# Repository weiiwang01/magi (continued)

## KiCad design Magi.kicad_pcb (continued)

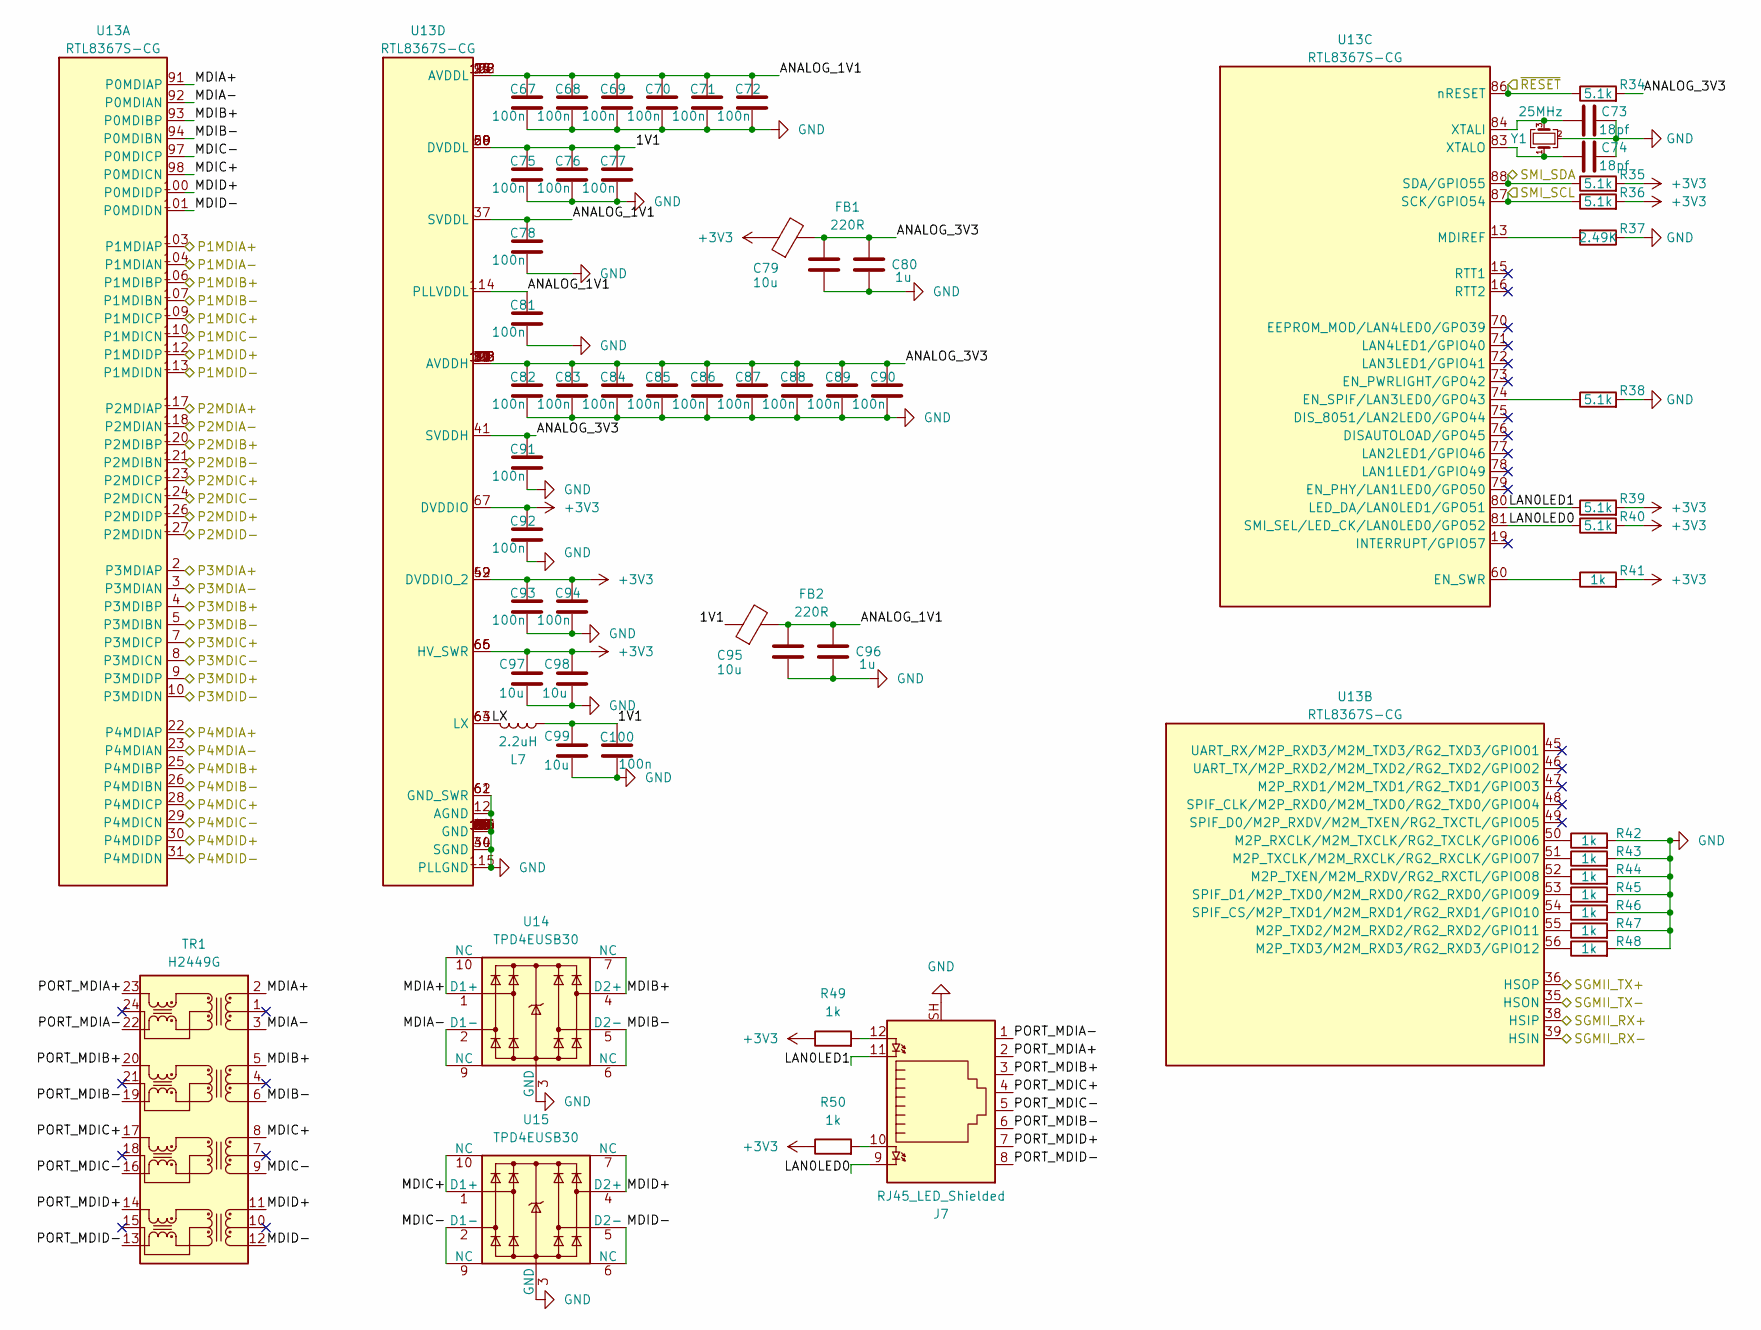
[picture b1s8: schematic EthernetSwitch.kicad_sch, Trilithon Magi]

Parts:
C67, C68, C69, C70, C71, C72, C75, C76, C77, C78, C81, C82, C83, C84, C85, C86, C87, C88, C89, C90, C91, C92, C93, C94, C100: 100n; C_0402_1005Metric; MPN CL05B104KB54PNC; LCSC C307331
C73, C74: 18pf; C_0402_1005Metric; MPN 0402CG180J500NT; LCSC C1549
C79, C95, C97, C98, C99: 10u; C_0603_1608Metric; MPN CL10A106MA8NRNC; LCSC C96446
C80, C96: 1u; C_0402_1005Metric; MPN CL05A105KO5NNNC; LCSC C29266
FB1, FB2: 220R; L_0603_1608Metric; MPN BLM18PG121SN1D; LCSC C14709
J7: RJ45_LED_Shielded; RJ45-TH_RJ45-005-202-11; MPN RJ45-005-202-11; LCSC C7421405
L7: 2.2uH; L_Changjiang_FTC404030S; MPN FTC404030S2R2MGCA; LCSC C39676081
R34, R35, R36, R38, R39, R40: 5.1k; R_0402_1005Metric; MPN 0402WGF5101TCE; LCSC C25905
R37: 2.49K; R_0402_1005Metric; MPN 0402WGF2491TCE; LCSC C25884
R41, R42, R43, R44, R45, R46, R47, R48, R49, R50: 1k; R_0402_1005Metric; MPN 0402WGF1001TCE; LCSC C11702
TR1: H2449G; RJ45-SMD_24P_L15.6-W8.7_H24308C; MPN H2449G; LCSC C5464748
U13: RTL8367S-CG; LQFP-128_14x14mm_P0.4mm; MPN RTL8367S-CG; LCSC C2760849
U14, U15: TPD4EUSB30; USON-10_2.5x1.0mm_P0.5mm; MPN TPD4EUSB30DQAR; LCSC C90627
Y1: 25MHz; Crystal_SMD_2016-4Pin_2.0x1.6mm; MPN XL7EL89COI-111YLC-25M; LCSC C20617996

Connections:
+3V3: C92.1, C93.1, C94.1, C97.1, C98.1, FB1.1, R35.2, R36.2, R39.2, R40.2, R41.2, R49.1, R50.1, U13.42 (DVDDIO_2), U13.59 (DVDDIO_2), U13.65 (HV_SWR), U13.66 (HV_SWR), U13.67 (DVDDIO); also elsewhere on the board
/Controller/ETH_P0+: U13.2 (P3MDIAP); also elsewhere on the board
/Controller/ETH_P0-: U13.3 (P3MDIAN); also elsewhere on the board
/Controller/ETH_P1+: U13.4 (P3MDIBP); also elsewhere on the board
/Controller/ETH_P1-: U13.5 (P3MDIBN); also elsewhere on the board
/Controller/PD7: R35.1, U13.88 (SDA/GPIO55); also elsewhere on the board
/Controller/PF10: R36.1, U13.87 (SCK/GPIO54); also elsewhere on the board
/Controller/PF11: R34.1, U13.86 (nRESET); also elsewhere on the board
/Ethernet Switch/1V1: C75.1, C76.1, C77.1, C99.1, C100.1, FB2.1, L7.2, U13.20 (DVDDL), U13.58 (DVDDL), U13.69 (DVDDL)
/Ethernet Switch/ANALOG_1V1: C67.1, C68.1, C69.1, C70.1, C71.1, C72.1, C78.1, C81.1, C95.1, C96.1, FB2.2, U13.6 (AVDDL), U13.14 (AVDDL), U13.27 (AVDDL), U13.37 (SVDDL), U13.95 (AVDDL), U13.108 (AVDDL), U13.114 (PLLVDDL), U13.122 (AVDDL)
/Ethernet Switch/ANALOG_3V3: C79.1, C80.1, C82.1, C83.1, C84.1, C85.1, C86.1, C87.1, C88.1, C89.1, C90.1, C91.1, FB1.2, R34.2, U13.11 (AVDDH), U13.17 (AVDDH), U13.21 (AVDDH), U13.33 (AVDDH), U13.41 (SVDDH), U13.82 (AVDDH), U13.90 (AVDDH), U13.102 (AVDDH), U13.116 (AVDDH), U13.128 (AVDDH)
/Ethernet Switch/LAN0LED0: J7.9, R40.1, U13.81 (SMI_SEL/LED_CK/LAN0LED0/GPO52)
/Ethernet Switch/LAN0LED1: J7.11, R39.1, U13.80 (LED_DA/LAN0LED1/GPO51)
/Ethernet Switch/LX: L7.1, U13.63 (LX), U13.64 (LX)
/Ethernet Switch/MDIA+: TR1.2 (TD1+), U13.91 (P0MDIAP), U14.1 (D1+), U14.10 (NC)
/Ethernet Switch/MDIA-: TR1.3 (TD1-), U13.92 (P0MDIAN), U14.2 (D1-), U14.9 (NC)
/Ethernet Switch/MDIB+: TR1.5 (TD2+), U13.93 (P0MDIBP), U14.4 (D2+), U14.7 (NC)
/Ethernet Switch/MDIB-: TR1.6 (TD2-), U13.94 (P0MDIBN), U14.5 (D2-), U14.6 (NC)
/Ethernet Switch/MDIC+: TR1.8 (TD3+), U13.98 (P0MDICN), U15.1 (D1+), U15.10 (NC)
/Ethernet Switch/MDIC-: TR1.9 (TD3-), U13.97 (P0MDICP), U15.2 (D1-), U15.9 (NC)
/Ethernet Switch/MDID+: TR1.11 (TD4+), U13.100 (P0MDIDP), U15.4 (D2+), U15.7 (NC)
/Ethernet Switch/MDID-: TR1.12 (TD4-), U13.101 (P0MDIDN), U15.5 (D2-), U15.6 (NC)
/Ethernet Switch/P1MDIA+: U13.103 (P1MDIAP); also elsewhere on the board
/Ethernet Switch/P1MDIA-: U13.104 (P1MDIAN); also elsewhere on the board
/Ethernet Switch/P1MDIB+: U13.106 (P1MDIBP); also elsewhere on the board
/Ethernet Switch/P1MDIB-: U13.107 (P1MDIBN); also elsewhere on the board
/Ethernet Switch/P1MDIC+: U13.109 (P1MDICP); also elsewhere on the board
/Ethernet Switch/P1MDIC-: U13.110 (P1MDICN); also elsewhere on the board
/Ethernet Switch/P1MDID+: U13.112 (P1MDIDP); also elsewhere on the board
/Ethernet Switch/P1MDID-: U13.113 (P1MDIDN); also elsewhere on the board
/Ethernet Switch/P2MDIA+: U13.117 (P2MDIAP); also elsewhere on the board
/Ethernet Switch/P2MDIA-: U13.118 (P2MDIAN); also elsewhere on the board
/Ethernet Switch/P2MDIB+: U13.120 (P2MDIBP); also elsewhere on the board
/Ethernet Switch/P2MDIB-: U13.121 (P2MDIBN); also elsewhere on the board
/Ethernet Switch/P2MDIC+: U13.123 (P2MDICP); also elsewhere on the board
/Ethernet Switch/P2MDIC-: U13.124 (P2MDICN); also elsewhere on the board
/Ethernet Switch/P2MDID+: U13.126 (P2MDIDP); also elsewhere on the board
/Ethernet Switch/P2MDID-: U13.127 (P2MDIDN); also elsewhere on the board
/Ethernet Switch/P3MDIC+: U13.7 (P3MDICP)
/Ethernet Switch/P3MDIC-: U13.8 (P3MDICN)
/Ethernet Switch/P3MDID+: U13.9 (P3MDIDP)
/Ethernet Switch/P3MDID-: U13.10 (P3MDIDN)
/Ethernet Switch/P4MDIA+: U13.22 (P4MDIAP); also elsewhere on the board
/Ethernet Switch/P4MDIA-: U13.23 (P4MDIAN); also elsewhere on the board
/Ethernet Switch/P4MDIB+: U13.25 (P4MDIBP); also elsewhere on the board
/Ethernet Switch/P4MDIB-: U13.26 (P4MDIBN); also elsewhere on the board
/Ethernet Switch/P4MDIC+: U13.28 (P4MDICP); also elsewhere on the board
/Ethernet Switch/P4MDIC-: U13.29 (P4MDICN); also elsewhere on the board
/Ethernet Switch/P4MDID+: U13.30 (P4MDIDP); also elsewhere on the board
/Ethernet Switch/P4MDID-: U13.31 (P4MDIDN); also elsewhere on the board
/Ethernet Switch/PORT_MDIA+: J7.2, TR1.23 (MX1+)
/Ethernet Switch/PORT_MDIA-: J7.1, TR1.22 (MX1-)
/Ethernet Switch/PORT_MDIB+: J7.3, TR1.20 (MX2+)
/Ethernet Switch/PORT_MDIB-: J7.6, TR1.19 (MX2-)
/Ethernet Switch/PORT_MDIC+: J7.4, TR1.17 (MX3+)
/Ethernet Switch/PORT_MDIC-: J7.5, TR1.16 (MX3-)
/Ethernet Switch/PORT_MDID+: J7.7, TR1.14 (MX4+)
/Ethernet Switch/PORT_MDID-: J7.8, TR1.13 (MX4-)
/Ethernet Switch/SGMII_RX+: U13.38 (HSIP); also elsewhere on the board
/Ethernet Switch/SGMII_RX-: U13.39 (HSIN); also elsewhere on the board
/Ethernet Switch/SGMII_TX+: U13.36 (HSOP); also elsewhere on the board
/Ethernet Switch/SGMII_TX-: U13.35 (HSON); also elsewhere on the board
GND: C67.2, C68.2, C69.2, C70.2, C71.2, C72.2, C73.1, C74.1, C75.2, C76.2, C77.2, C78.2, C79.2, C80.2, C81.2, C82.2, C83.2, C84.2, C85.2, C86.2, C87.2, C88.2, C89.2, C90.2, C91.2, C92.2, C93.2, C94.2, C95.2, C96.2, C97.2, C98.2, C99.2, C100.2, J7.SH, R37.1, R38.2, R42.2, R43.2, R44.2, R45.2, R46.2, R47.2, R48.2, U13.1 (GND), U13.12 (AGND), U13.18 (GND), U13.24 (GND), U13.32 (GND), U13.34 (SGND), U13.40 (SGND), U13.43 (GND), U13.44 (GND), U13.57 (GND), U13.61 (GND_SWR), U13.62 (GND_SWR), U13.68 (GND), U13.85 (GND), U13.89 (GND), U13.96 (GND), U13.99 (GND), U13.105 (GND), U13.111 (GND), U13.115 (PLLGND), U13.119 (GND), U13.125 (GND), U14.3 (GND), U14.8 (GND), U15.3 (GND), U15.8 (GND), Y1.2 (G), Y1.4 (G); also elsewhere on the board
unnamed: J7.10, R50.2
unnamed: J7.12, R49.2
unnamed: R42.1, U13.50 (M2P_RXCLK/M2M_TXCLK/RG2_TXCLK/GPIO06)
unnamed: R43.1, U13.51 (M2P_TXCLK/M2M_RXCLK/RG2_RXCLK/GPIO07)
unnamed: R47.1, U13.55 (M2P_TXD2/M2M_RXD2/RG2_RXD2/GPIO11)
unnamed: R48.1, U13.56 (M2P_TXD3/M2M_RXD3/RG2_RXD3/GPIO12)
unnamed: R44.1, U13.52 (M2P_TXEN/M2M_RXDV/RG2_RXCTL/GPIO08)
unnamed: R46.1, U13.54 (SPIF_CS/M2P_TXD1/M2M_RXD1/RG2_RXD1/GPIO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)
unnamed: R45.1, U13.53 (SPIF_D1/M2P_TXD0/M2M_RXD0/RG2_RXD0/GPIO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)
unnamed: R38.1, U13.74 (EN_SPIF/LAN3LED0/GPO43)
unnamed: R41.1, U13.60 (EN_SWR)
unnamed: R37.2, U13.13 (MDIREF)
unnamed: C73.2, U13.84 (XTALI), Y1.3
unnamed: C74.2, U13.83 (XTALO), Y1.1

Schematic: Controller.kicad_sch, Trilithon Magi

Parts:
BT1: CR1220; BAT-SMD_MY-1220-03; MPN MY-1220-04; LCSC C2979172
C101, C102, C104, C105, C106, C107, C109, C111, C113, C114, C115, C117, C121, C122, C123, C124, C125, C126, C190, C191: 100n; C_0402_1005Metric; MPN CL05B104KB54PNC; LCSC C307331
C103, C108, C110: 4.7u; C_0603_1608Metric; MPN CL10A475KO8NNNC; LCSC C19666
C112: 10u; C_0603_1608Metric; MPN CL10A106MA8NRNC; LCSC C96446
C116, C118: 1u; C_0402_1005Metric; MPN CL05A105KO5NNNC; LCSC C29266
C119, C120, C127, C128: 18pf; C_0402_1005Metric; MPN 0402CG180J500NT; LCSC C1549
D7, D8, D9, D10: WS2812C; LED-SMD_4P-L4.0-W1.7_DCS; MPN WS2812C-4020-V6; LCSC C55109523
J8: USB_C_Receptacle; USB-C-SMD_TYPE-C-GT-USB-7007C; MPN GT-USB-9007A; LCSC C48533148
J9: Conn_02x04; PinHeader_2x04_P1.27mm_Vertical_SMD_MountingPegs; MPN HX PZ1.27-2x4P TP-D; LCSC C42454109
Q1: DMN32D2LFB4; Diodes_DFN1006-3; MPN DMN32D2LFB4-7; LCSC C151382
R51, R52, R59, R60: 100k; R_0402_1005Metric; MPN 0402WGF1003TCE; LCSC C25741
R53, R54, R55, R57, R58, R61, R62, R113, R116, R117: 5.1k; R_0402_1005Metric; MPN 0402WGF5101TCE; LCSC C25905
R56: 12k; R_0402_1005Metric; MPN 0402WGF1202TCE; LCSC C25752
SW1: SW_Push; SW-SMD_L4.7-W3.5-P3.35-EH; MPN GT-TC018B-H0375-L1; LCSC C2762970
TP4, TP5, TP6, TP7, TP13: TestPoint; TestPoint_Pad_D1.5mm
U16: USB2514B; QFN-36-1EP_6x6mm_P0.5mm_EP3.7x3.7mm; MPN USB2514B-AEZC-TR; LCSC C16251
U17: CH390H; QFN-32-1EP_5x5mm_P0.5mm_EP3.45x3.45mm; MPN CH390H; LCSC C7498452
U18: STM32G0B1VETx; LQFP-100_14x14mm_P0.5mm; MPN STM32G0B1VET6; LCSC C2829192
U19: TPD4EUSB30; USON-10_2.5x1.0mm_P0.5mm; MPN TPD4EUSB30DQAR; LCSC C90627
U45: ATECC608B-MAHCZ; DFN-8-1EP_3x2mm_P0.5mm_EP1.3x1.5mm; MPN ATECC608B-MAHCZ; LCSC C1518770
U46: CAT25512HU5I-GT3; DFN-8-1EP_3x2mm_P0.5mm_EP0.9x1.4mm; MPN CAT25512HU5I-GT3; LCSC C463684
Y2: 25MHz; Crystal_SMD_2016-4Pin_2.0x1.6mm; MPN XL7EL89COI-111YLC-25M; LCSC C20617996
Y3: 24MHz; Crystal_SMD_2016-4Pin_2.0x1.6mm; MPN XL7EL89COI-111YLC-24M; LCSC C22434877
Y4: 32.768kHz; Crystal_SMD_2012-2Pin_2.0x1.2mm; MPN SX201232768K2GHCZ2T; LCSC C5271201

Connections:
+3V3: C101.2, C102.2, C103.1, C104.2, C105.2, C106.2, C107.2, C108.1, C109.2, C110.1, C111.2, C112.1, C113.2, C114.2, C115.2, C190.2, C191.2, J9.6, R54.2, R55.2, R57.2, R58.2, R59.1, R113.2, R116.1, R117.1, U16.5 (VDDA33), U16.10 (VDDA33), U16.15 (VDD33), U16.23 (VDD33), U16.29 (VDDA33), U16.36 (VDDA33), U17.15 (AVDD33), U17.21 (VDDIO), U17.29 (AVDD33), U18.13 (VDD), U18.64 (VDD), U45.8 (VCC), U46.3 (~WP), U46.7 (~HOLD), U46.8 (VCC); also elsewhere on the board
+5V: D7.2 (VDD), D8.2 (VDD), D9.2 (VDD), D10.2 (VDD), J9.8; also elsewhere on the board
/Controller/ETH_P0+: C123.2; also elsewhere on the board
/Controller/ETH_P0-: C124.2; also elsewhere on the board
/Controller/ETH_P1+: C125.2; also elsewhere on the board
/Controller/ETH_P1-: C126.2; also elsewhere on the board
/Controller/HUB_USB2_1_D+: U16.2 (USBDP_DN1/PRT_DIS_P1); also elsewhere on the board
/Controller/HUB_USB2_1_D-: U16.1 (USBDM_DN1/PRT_DIS_M1); also elsewhere on the board
/Controller/HUB_USB2_2_D+: U16.4 (USBDP_DN2/PRT_DIS_P2); also elsewhere on the board
/Controller/HUB_USB2_2_D-: U16.3 (USBDM_DN2/PRT_DIS_M2); also elsewhere on the board
/Controller/HUB_USB2_3_D+: U16.7 (USBDP_DN3/PRT_DIS_P3); also elsewhere on the board
/Controller/HUB_USB2_3_D-: U16.6 (USBDM_DN3/PRT_DIS_M3); also elsewhere on the board
/Controller/HUB_USB2_4_D+: U16.9 (USBDP_DN4/PRT_DIS_P4), U18.71 (PA10/PA12)
/Controller/HUB_USB2_4_D-: U16.8 (USBDM_DN4/PRT_DIS_M4), U18.70 (PA9/PA11)
/Controller/MDIR+: C126.1, U17.3 (MDIRP)
/Controller/MDIR-: C125.1, U17.4 (MDIRN)
/Controller/MDIT+: C124.1, U17.6 (MDITP)
/Controller/MDIT-: C123.1, U17.7 (MDITN)
/Controller/PA0_SPI2_SCK: U17.18 (SCK), U18.25 (PA0)
/Controller/PA1: U18.26 (PA1); also elsewhere on the board
/Controller/PA3: U18.28 (PA3); also elsewhere on the board
/Controller/PA4_ADC1_IN4: U18.29 (PA4); also elsewhere on the board
/Controller/PA6_I2C3_SDA: U18.31 (PA6); also elsewhere on the board
/Controller/PA7_I2C3_SCL: U18.32 (PA7); also elsewhere on the board
/Controller/PA15: U18.75 (PA15); also elsewhere on the board
/Controller/PB0_MCU_BUTTON: R113.1, SW1.1, U18.35 (PB0)
/Controller/PB1: U18.36 (PB1); also elsewhere on the board
/Controller/PB2_ADC1_IN10: U18.37 (PB2); also elsewhere on the board
/Controller/PB3_SPI3_SCK: J9.1, U18.91 (PB3), U46.6 (SCK)
/Controller/PB4_SPI3_MISO: J9.2, U18.92 (PB4), U46.2 (MISO)
/Controller/PB5_SPI3_MOSI: J9.4, U18.93 (PB5), U46.5 (MOSI)
/Controller/PB6: U18.98 (PB6); also elsewhere on the board
/Controller/PB8_I2C1_SCL: U18.100 (PB8); also elsewhere on the board
/Controller/PB9_I2C1_SDA: U18.1 (PB9); also elsewhere on the board
/Controller/PB10_ADC1_IN11: U18.49 (PB10); also elsewhere on the board
/Controller/PB11_ADC1_IN15: U18.50 (PB11); also elsewhere on the board
/Controller/PB12_ADC1_IN16: U18.51 (PB12); also elsewhere on the board
/Controller/PB13_I2C2_SCL: U18.52 (PB13); also elsewhere on the board
/Controller/PB14_I2C2_SDA: U18.53 (PB14); also elsewhere on the board
/Controller/PC0: U17.17 (SCS), U18.21 (PC0)
/Controller/PC1: U18.22 (PC1); also elsewhere on the board
/Controller/PC2_SPI2_MISO: U17.20 (SDO/MISO), U18.23 (PC2)
/Controller/PC3_SPI2_MOSI: U17.19 (SDI/MOSI), U18.24 (PC3)
/Controller/PC4_USART1_TX: U18.33 (PC4); also elsewhere on the board
/Controller/PC5_USART1_RX: U18.34 (PC5); also elsewhere on the board
/Controller/PC7: R117.2, U18.58 (PC7), U46.1 (~CS)
/Controller/PC8: U18.76 (PC8); also elsewhere on the board
/Controller/PC9: U18.77 (PC9); also elsewhere on the board
/Controller/PC10_USART4_TX: U18.2 (PC10); also elsewhere on the board
/Controller/PC11_USART4_RX: U18.3 (PC11); also elsewhere on the board
/Controller/PC12: U18.7 (PC12); also elsewhere on the board
/Controller/PC13: U18.8 (PC13); also elsewhere on the board
/Controller/PD4: U18.82 (PD4); also elsewhere on the board
/Controller/PD5_USART2_TX: U18.83 (PD5); also elsewhere on the board
/Controller/PD6_USART2_RX: U18.84 (PD6); also elsewhere on the board
/Controller/PD7: U18.85 (PD7); also elsewhere on the board
/Controller/PD8_USART3_TX: U18.59 (PD8); also elsewhere on the board
/Controller/PD9_USART3_RX: U18.60 (PD9); also elsewhere on the board
/Controller/PD10: U18.61 (PD10); also elsewhere on the board
/Controller/PD11_SPI3_INT: J9.5, U18.62 (PD11)
/Controller/PD12: U18.65 (PD12); also elsewhere on the board
/Controller/PD13: U18.66 (PD13); also elsewhere on the board
/Controller/PD14: U18.67 (PD14); also elsewhere on the board
/Controller/PD15: U18.68 (PD15); also elsewhere on the board
/Controller/PE0_SPI3_CS: J9.3, U18.94 (PE0)
/Controller/PE1: U18.95 (PE1); also elsewhere on the board
/Controller/PE2: U18.96 (PE2); also elsewhere on the board
/Controller/PE3_TIM3_CH1: D7.1 (DIN), U18.97 (PE3)
/Controller/PE4: U18.4 (PE4); also elsewhere on the board
/Controller/PE5: R57.1, U16.24 (SCL/SMBCLK/CFG_SEL0), U18.5 (PE5)
/Controller/PE6: R58.1, U16.22 (SDA/SMBDATA/NON_REM1), U18.6 (PE6)
/Controller/PE7: U18.40 (PE7); also elsewhere on the board
/Controller/PE8: U18.41 (PE8); also elsewhere on the board
/Controller/PE9: U18.42 (PE9); also elsewhere on the board
/Controller/PE10_USART5_TX: TP7.1 (1_1), U18.43 (PE10)
/Controller/PE11: U18.44 (PE11); also elsewhere on the board
/Controller/PE12: U18.45 (PE12); also elsewhere on the board
/Controller/PE13: U18.46 (PE13); also elsewhere on the board
/Controller/PE14: U18.47 (PE14); also elsewhere on the board
/Controller/PE15: U18.48 (PE15); also elsewhere on the board
/Controller/PF0: U18.15 (PF0); also elsewhere on the board
/Controller/PF1: R54.1, U16.26 (RESET_N), U18.16 (PF1)
/Controller/PF3: U18.18 (PF3); also elsewhere on the board
/Controller/PF4: U18.19 (PF4); also elsewhere on the board
/Controller/PF5: U18.20 (PF5); also elsewhere on the board
/Controller/PF6: U18.38 (PF6); also elsewhere on the board
/Controller/PF7: U18.39 (PF7); also elsewhere on the board
/Controller/PF8: U18.72 (PF8); also elsewhere on the board
/Controller/PF9_USART6_TX: R116.2, TP13.1 (1_1), U18.86 (PF9), U45.5 (SDA)
/Controller/PF10: U18.87 (PF10); also elsewhere on the board
/Controller/PF11: U18.88 (PF11); also elsewhere on the board
/Controller/PF12: R53.1, U17.27 (RSTB), U18.89 (PF12)
/Controller/PF13: U17.24 (INT), U18.90 (PF13)
/Controller/SWCLK: TP6.1 (1_1), U18.74 (PA14)
/Controller/SWDIO: TP5.1 (1_1), U18.73 (PA13)
/Controller/UCPD1_CC1: U18.55 (PA8), U18.56 (PA9/UCPD1_DBCC1); also elsewhere on the board
/Controller/UCPD1_CC2: U18.54 (PB15), U18.69 (PA10/UCPD1_DBCC2); also elsewhere on the board
/Controller/UCPD2_CC1: U18.78 (PD0), U18.79 (PD1); also elsewhere on the board
/Controller/UCPD2_CC2: U18.80 (PD2), U18.81 (PD3); also elsewhere on the board
/Controller/USB_PORT_D+: J8.A6 (D+), J8.B6 (D+), U16.31 (USBDP_UP), U19.1 (D1+), U19.10 (NC)
/Controller/USB_PORT_D-: J8.A7 (D-), J8.B7 (D-), U16.30 (USBDM_UP), U19.2 (D1-), U19.9 (NC)
/Controller/VBUS_DET: J8.A4 (VBUS), J8.A9 (VBUS), J8.B4 (VBUS), J8.B9 (VBUS), R51.1, U19.4 (D2+), U19.7 (NC)
/Controller/~MCU_RST: C117.2, R55.1, TP4.1 (1_1), U18.17 (PF2)
/LSCO: U18.27 (PA2); also elsewhere on the board
/Unit 1/CM_3V3: U18.99 (PB7); also elsewhere on the board
/Unit 2/CM_3V3: U18.30 (PA5); also elsewhere on the board
/Unit 3/CM_3V3: U18.57 (PC6); also elsewhere on the board
GND: C101.1, C102.1, C103.2, C104.1, C105.1, C106.1, C107.1, C108.2, C109.1, C110.2, C111.1, C112.2, C113.1, C114.1, C115.1, C116.1, C117.1, C118.1, C119.1, C120.1, C121.2, C122.2, C127.1, C128.1, C190.1, C191.1, D7.4 (VSS), D8.4 (VSS), D9.4 (VSS), D10.4 (VSS), J8.A1 (GND), J8.A12 (GND), J8.B1 (GND), J8.B12 (GND), J8.S1 (SHIELD), J9.7, Q1.2 (S), R52.2, R53.2, R56.2, R60.1, R61.2, R62.2, SW1.2, U16.11 (TEST), U16.37 (VSS), U17.5 (GND), U17.32 (GND), U17.33 (EP), U18.14 (VSS), U18.63 (VSS), U19.3 (GND), U19.8 (GND), U45.4 (GND), U45.9 (EP), U46.4 (GND), U46.9 (GND), Y2.2 (G), Y2.4 (G), Y3.2 (G), Y3.4 (G); also elsewhere on the board
unnamed: BT1.1 (+), Q1.1 (G), U18.11 (VBAT)
unnamed: BT1.2 (-), Q1.3 (D)
unnamed: D7.3 (DOUT), D8.1 (DIN)
unnamed: D8.3 (DOUT), D9.1 (DIN)
unnamed: D9.3 (DOUT), D10.1 (DIN)
unnamed: J8.A5 (CC1), R62.1
unnamed: J8.B5 (CC2), R61.1
unnamed: C122.1, U16.14 (CRFILT)
unnamed: R60.2, U16.25 (HS_IND/CFG_SEL1)
unnamed: C121.1, U16.34 (PLLFILT)
unnamed: R56.1, U16.35 (RBIAS)
unnamed: R59.2, U16.28 (SUSP_IND/LOCAL_PWR/NON_REM0)
unnamed: R51.2, R52.1, U16.27 (VBUS_DET)
unnamed: C119.2, U16.33 (XTALIN/CLKIN), Y3.1
unnamed: C120.2, U16.32 (XTALOUT), Y3.3
unnamed: C118.2, U17.1 (VDDK), U17.2 (RSVD)
unnamed: U17.30 (XI), Y2.3
unnamed: U17.31 (XO), Y2.1
unnamed: C127.2, U18.9 (PC14), Y4.2
unnamed: C128.2, U18.10 (PC15), Y4.1
unnamed: C116.2, U18.12 (VREF+)

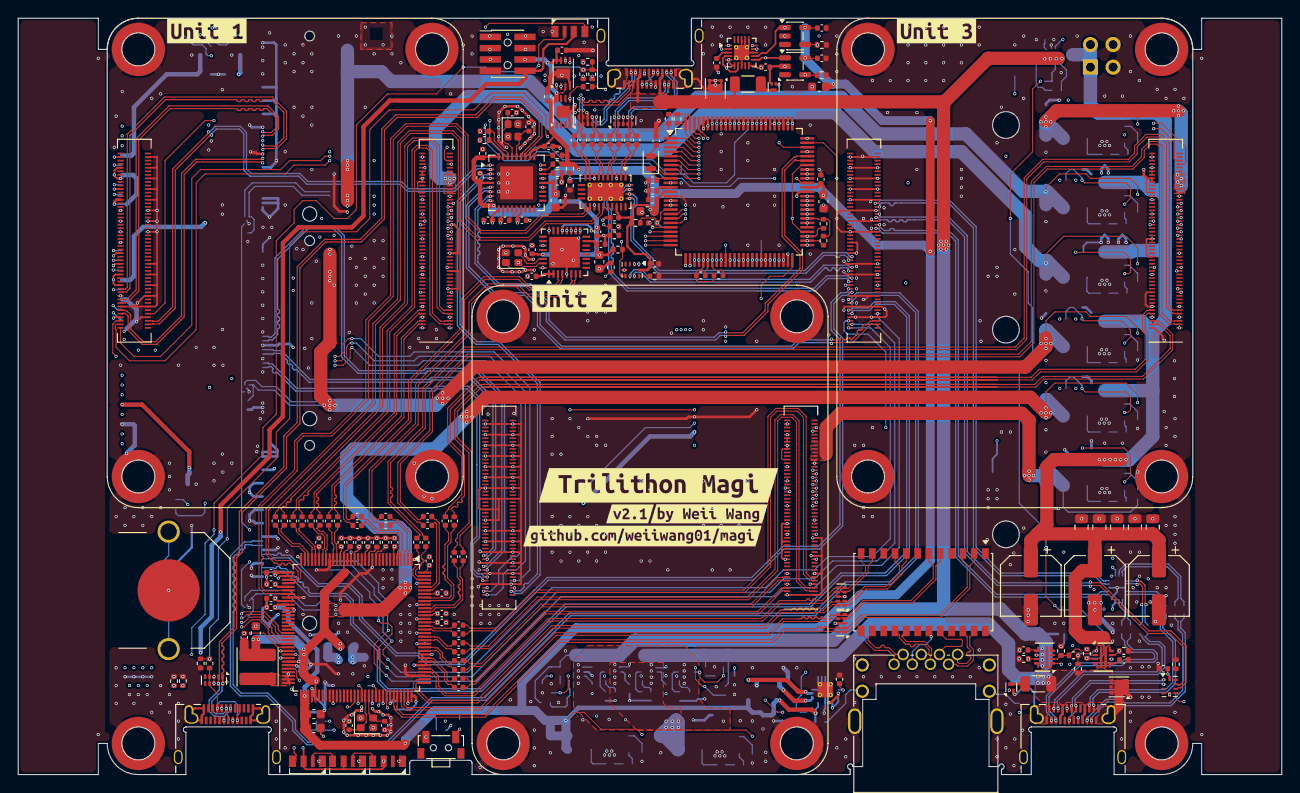
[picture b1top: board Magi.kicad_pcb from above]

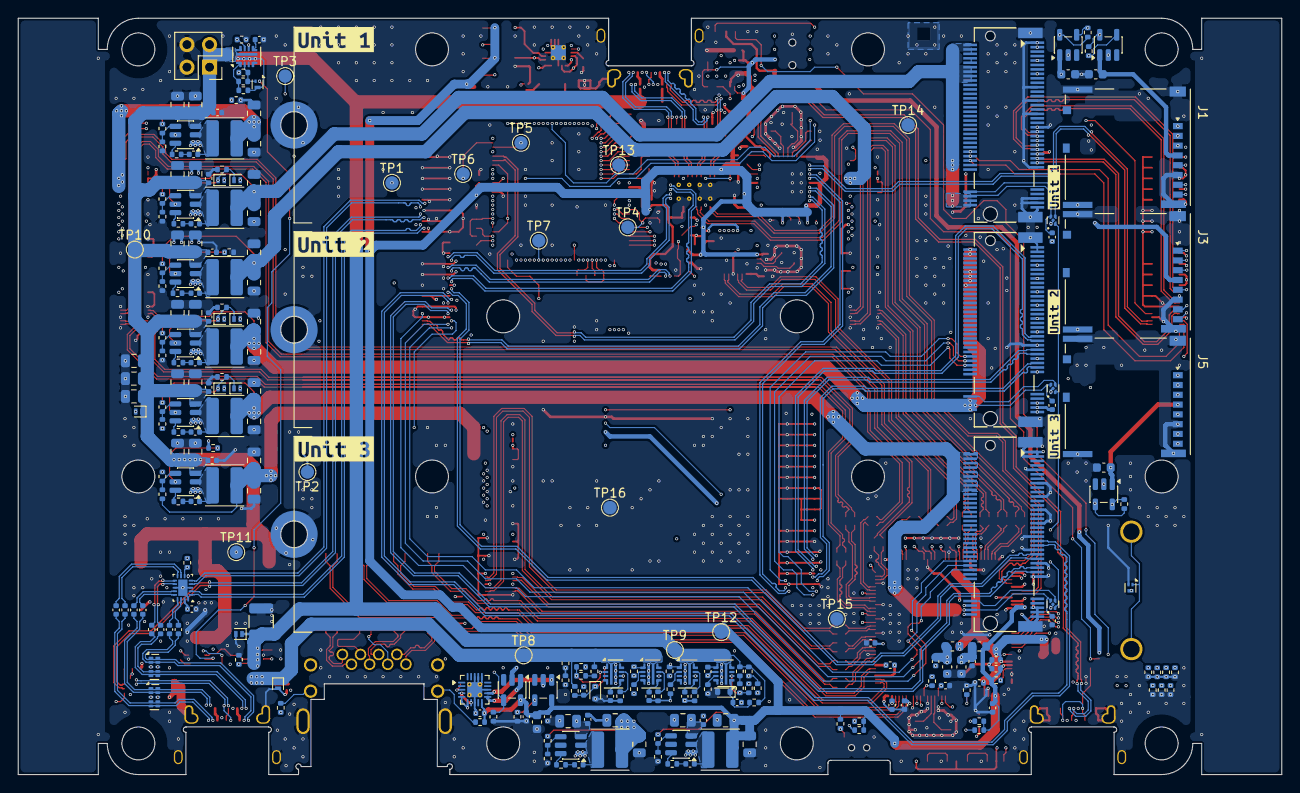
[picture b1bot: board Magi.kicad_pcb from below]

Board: 6 copper layers, 142.0 x 85.0 mm, 436 parts (244 on the bottom side), 406 nets.

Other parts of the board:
kibuzzard-6A5B14ED: G***; kibuzzard-6A5B14ED
kibuzzard-6A5B154C: G***; kibuzzard-6A5B154C
kibuzzard-6A5B1551: G***; kibuzzard-6A5B1551
kibuzzard-6AC565B3: G***; kibuzzard-6AC565B3
kibuzzard-69C4E3CF: G***; kibuzzard-69C4E3CF
kibuzzard-69C4E40D: G***; kibuzzard-69C4E40D
kibuzzard-69C4E42D: G***; kibuzzard-69C4E42D
kibuzzard-69C509A0: G***; kibuzzard-69C509A0
kibuzzard-69C5095C: G***; kibuzzard-69C5095C
kibuzzard-69C5098A: G***; kibuzzard-69C5098A
kibuzzard-69C50949: G***; kibuzzard-69C50949
kibuzzard-69C50974: G***; kibuzzard-69C50974
kibuzzard-69C50981: G***; kibuzzard-69C50981

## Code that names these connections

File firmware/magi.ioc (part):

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Mcu.Name=STM32G0B1V(B-C-E)Tx
Mcu.Package=LQFP100
Mcu.UserName=STM32G0B1VETx
PA10.Mode=EnableDeadBattery
PA10.Signal=UCPD1_DBCC2
PA11\ [PA9].Mode=Device
PA11\ [PA9].Signal=USB_DM
PA12\ [PA10].Mode=Device
PA12\ [PA10].Signal=USB_DP
PA2.Mode=Clock-out-LSCO
PA2.Signal=RCC_LSCO
PA8.Mode=Dual_Role_AllSignals
PA8.Signal=UCPD1_CC1
PA9.Mode=EnableDeadBattery
PA9.Signal=UCPD1_DBCC1
PB15.Mode=Dual_Role_AllSignals
PB15.Signal=UCPD1_CC2
PC14-OSC32_IN\ (PC14).Mode=LSE-External-Oscillator
PC14-OSC32_IN\ (PC14).Signal=RCC_OSC32_IN
PC15-OSC32_OUT\ (PC15).Mode=LSE-External-Oscillator
PC15-OSC32_OUT\ (PC15).Signal=RCC_OSC32_OUT
PD0.Mode=Dual_Role_AllSignals
PD0.Signal=UCPD2_CC1
PD1.Mode=EnableDeadBattery
PD1.Signal=UCPD2_DBCC1
PD2.Mode=Dual_Role_AllSignals
PD2.Signal=UCPD2_CC2
PD3.Mode=EnableDeadBattery
PD3.Signal=UCPD2_DBCC2
RCC.HSE_VALUE=8000000
RCC.SYSCLKFreq_VALUE=64000000
RCC.SYSCLKSource=RCC_SYSCLKSOURCE_PLLCLK
board=custom

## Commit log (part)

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2024-10-29 Magi v1.0
2024-11-12 Upload the case design for Magi v1.0
